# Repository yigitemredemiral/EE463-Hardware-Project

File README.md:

# EE463 Hardware Project: 60 W Synchronous Buck Converter

METU EE463 Static Power Conversion I, Fall 2026, term project
([specification](https://github.com/odtu/EE463/blob/master/Hardware%20Project/EE463%20Hardware%20Project.md)).

20–48 V DC input, 12 V / 5 A (60 W) regulated output, closed-loop peak current-mode control, one input source,
own 4-layer PCB. Bonus targets: 90 W overload, 7.5 A-class current limit, reverse-polarity protection, efficiency,
line/load transient comparison.

| | |
|---|---|
| Topology | Synchronous buck, 94.3 kHz |
| Controller | Analog Devices LTC3895 (150 V, peak current mode), self-supplied from VIN and then from VOUT (EXTVCC) |
| Power stage | Infineon BSC040N08NS5 (high side), BSC026N08NS5 (low side), Coilcraft XAL1510-333 33 µH, 2 × 330 µF polymer |
| Protection | LM74700-Q1 ideal diode (reverse polarity), average current limit 7.88 A (LT6105 + LT6654 + LT1636), RUN/OVLO |
| PCB | 4 layers, 90 × 65 mm, KiCad 10 |
| Simulated efficiency | 97.3 % average at 60 W over 20/24/36/48 V *(simulation, not measured)* |

## Status (19 November 2026)

| Deadline | Item | Status |
|---|---|---|
| 22 Nov | Pre-report | Draft: [`reports/PreReport.md`](reports/PreReport.md) |
| 24–25 Nov | Feedback session | Schematic, PCB and simulations ready |
| 30 Nov | PCB files for sponsored production | Gerber/drill not generated yet (after the feedback session) |
| 4 Jan | Hardware demo | — |

Nothing has been ordered or sent to a manufacturer yet. No hardware measurement exists yet.

## Repository map

| Folder | Content |
|---|---|
| [`hardware/kicad_RevF4/`](hardware/kicad_RevF4/) | **Current board.** RevF2 schematic with the re-routed signals, constant-width power tracks, pad stitching pours and the course PCB-checker fixes. Passes the [course PCB checker](https://github.com/odtu/EE463/tree/master/Hardware%20Project/PCB-Checker) with 0 errors at 5 A and 7.5 A (only warning: 4 layers). Settings and waiver in `pcb_checker.json`. |
| [`hardware/kicad_RevF2/`](hardware/kicad_RevF2/) | KiCad 10 project. The schematic is drawn with wires (one A3 sheet, five blocks); the PCB is the RevF1 layout with 0805 parts, CCATH1 and the new part numbers. Printable copies: [schematic](hardware/kicad_RevF2/EE463_Buck_RevF2_schematic.pdf), [assembly top](hardware/kicad_RevF2/EE463_Buck_RevF2_assembly_top.pdf), [assembly bottom](hardware/kicad_RevF2/EE463_Buck_RevF2_assembly_bottom.pdf). |
| [`simulation/ltspice_RevF2/`](simulation/ltspice_RevF2/) | Drawn LTspice schematic of the final design (`EE463_Buck_RevF2.asc`) with its symbols and models. Open it in LTspice and run. |
| [`simulation/ltspice_RevF1_runs/`](simulation/ltspice_RevF1_runs/) | All RevF1 netlists, logs and scripts behind the numbers in the reports. |
| [`simulation/compensation_AB/`](simulation/compensation_AB/) | Loop-gain and transient comparison of compensation A and B. |
| [`calculations/`](calculations/) | Analytical design (duty cycle, ripple, stresses, losses, thermal). |
| [`bom/`](bom/) | Bill of materials in the course format, full BOM with datasheets, ordering notes. |
| [`reports/FinalReport/`](reports/FinalReport/) | Full report ([PDF](reports/FinalReport/EE463_Final_Report.pdf); design, circuit simulation, PCB and checker, 5-minute thermal analysis). Compile `main.tex` with pdfLaTeX; all numbers come from `values.tex`. PCB-checker reports in `pcb_checker/`. |
| [`simulation/analysis_RevF4/`](simulation/analysis_RevF4/) | Scripts behind the final report: LTspice batch runs, loss breakdown, loop gain, 4-layer thermal model, copper current flow. |
| [`reports/`](reports/) | Pre-report, control-loop section, figures. |
| [`docs/design_review/`](docs/design_review/) | Design review and revision notes (Turkish), RevD5E1 → RevF1 → RevF2. |
| [`tools/`](tools/) | Scripts that generate the schematic, the LTspice drawing, the BOM and run the checks. |

## Revision history

| Revision | Change |
|---|---|
| RevD5E1 | First complete design (Yasin): LTC3895, 145 kHz, Schottky reverse protection |
| RevF1 | Review and two rounds of changes: 94.3 kHz, BSC040 high side, compensation A, current limit 7.88 A, OVLO 58 V, LM74700 ideal diode, hot-loop capacitors, thermal vias, layout fixes |
| RevF2 | Readable schematic (KiCad and LTspice, drawn with wires); 24 of 30 former 0603 parts enlarged to 0805 (course rule) by moving them ≤ 0.38 mm, 6 resistors stay 0603; Vishay parts replaced (course rule: no Israel-made parts); CCATH1 1 µF / 100 V added at the LM74700 CATHODE (approved in the RevF1 review); BOM in the course format with prices and datasheets. ERC 0, DRC 0, parity 0. |
| **RevF4** | Signal re-route; constant track widths; pours instead of pad-to-via tracks; SW and Q2 source pours; course PCB-checker fixes (via-to-drill spacing, no vias in small pads, 0.4 mm via arrays at RS1 and Q2 sources). DRC 0, parity 0. |

## Checks

```bash
bash tools/run_checks.sh
```

- KiCad schematic connectivity = RevF1 netlist (net-by-net comparison), ERC, DRC with schematic parity.
- LTspice drawing: LTspice's own netlist of the `.asc` compared element by element with the RevF1 simulation netlist.

## Tools used

KiCad 10.0, LTspice 26.0, Python 3.12 (numpy, matplotlib). AI tools (Claude) were used for simulation scripting,
schematic drawing and checks; every result was checked against simulation, the datasheets or the netlist, as the
course rules require.

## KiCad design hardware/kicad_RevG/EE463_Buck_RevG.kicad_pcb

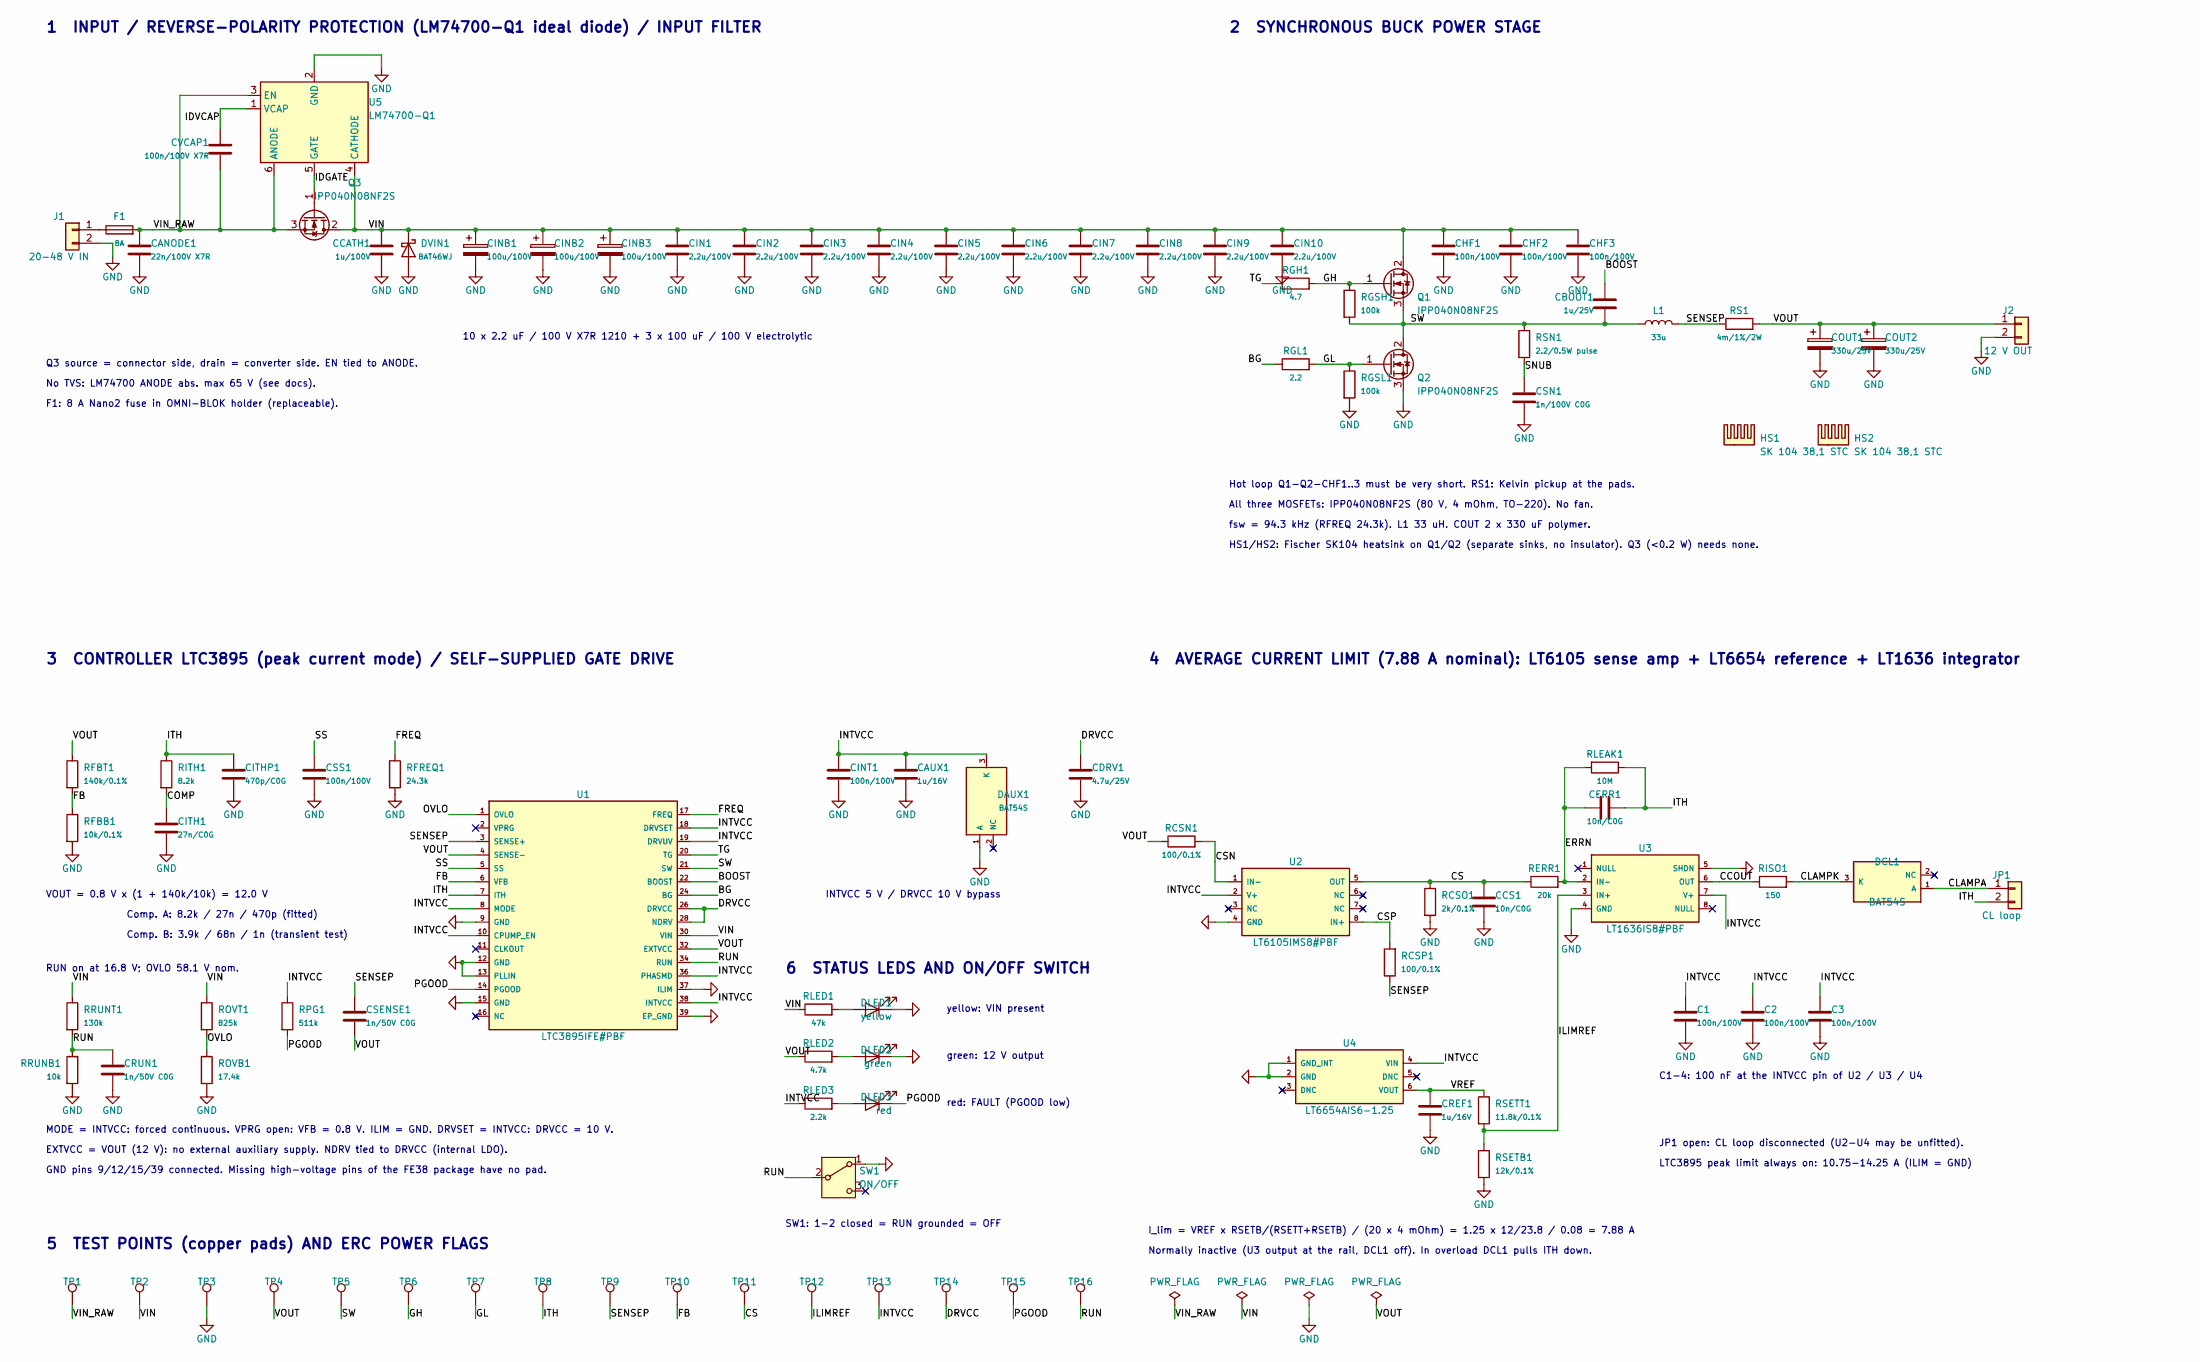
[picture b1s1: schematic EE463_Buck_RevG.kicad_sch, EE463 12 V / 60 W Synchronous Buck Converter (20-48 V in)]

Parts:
C1, C2, C3: 100n/100V; C_0805_2012Metric; MPN C2012X7R2A104K125AA
CANODE1: 22n/100V X7R; C_0805_2012Metric; MPN GRM21BR72A223KA01L
CAUX1: 1u/16V; C_0805_2012Metric; MPN CC0805KKX7R7BB105
CBOOT1: 1u/25V; C_0805_2012Metric; MPN CC0805KKX7R8BB105
CCATH1: 1u/100V; C_0805_2012Metric; MPN C2012X7S2A105K125AB
CCS1: 10n/C0G; C_0805_2012Metric; MPN CL21C103JBFNNNE
CDRV1: 4.7u/25V; C_0805_2012Metric; MPN CL21A475KAQNNNE
CERR1: 10n/C0G; C_0805_2012Metric; MPN CL21C103JBFNNNE
CHF1, CHF2, CHF3: 100n/100V; C_0805_2012Metric; MPN C2012X7R2A104K125AA
CIN1, CIN2, CIN3, CIN4, CIN5, CIN6, CIN7, CIN8, CIN9, CIN10: 2.2u/100V; C_1210_3225Metric; MPN GRM32ER72A225KA35L
CINB1, CINB2, CINB3: 100u/100V; CP_Radial_D10.0mm_P5.00mm; MPN 100ZLH100MEFC10X20
CINT1: 100n/100V; C_0805_2012Metric; MPN C2012X7R2A104K125AA
CITH1: 27n/C0G; C_0805_2012Metric; MPN GRM2165C1H273JA01D
CITHP1: 470p/C0G; C_0805_2012Metric; MPN CL21C471JBANNNC
COUT1, COUT2: 330u/25V; CP_Elec_10x12.6; MPN 25SVPF330M
CREF1: 1u/16V; C_0805_2012Metric; MPN CC0805KKX7R7BB105
CRUN1: 1n/50V C0G; C_0805_2012Metric; MPN CC0805JRNPO9BN102
CSENSE1: 1n/50V C0G; C_0805_2012Metric; MPN CC0805JRNPO9BN102
CSN1: 1n/100V C0G; C_0805_2012Metric; MPN C2012C0G2A102J060AA
CSS1: 100n/100V; C_0805_2012Metric; MPN C2012X7R2A104K125AA
CVCAP1: 100n/100V X7R; C_0805_2012Metric; MPN C2012X7R2A104K125AA
DAUX1: BAT54S; SOT-23; MPN BAT54S-HT
DCL1: BAT54S; SOT-23; MPN BAT54S-HT
DLED1: yellow; LED_0805_2012Metric; MPN 150080YS75000
DLED2: green; LED_0805_2012Metric; MPN 150080GS75000
DLED3: red; LED_0805_2012Metric; MPN 150080RS75000
DVIN1: BAT46WJ; D_SOD-323F; MPN BAT46WJ,115
F1: 8A; Fuseholder_Littelfuse_Nano2_154x; MPN 0154008.DR
HS1, HS2: SK 104 38,1 STC; Heatsink_Fischer_SK104-STC-STIC_35x13mm_2xDrill2.5mm; MPN SK 104 38,1 STC
J1: 20-48 V IN; TerminalBlock_Phoenix_MKDS-1,5-2-5.08_1x02_P5.08mm_Horizont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; MPN 1715721
J2: 12 V OUT; TerminalBlock_Phoenix_MKDS-1,5-2-5.08_1x02_P5.08mm_Horizont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; MPN 1715721
JP1: CL loop; PinHeader_1x02_P2.54mm_Vertical; MPN 61300211121
L1: 33u; L_XAL1510_WE-XHMI1510_Dual; MPN XAL1510-333MED
Q1, Q2, Q3: IPP040N08NF2S; TO-220-3_Vertical; MPN IPP040N08NF2SAKMA1
RCSN1: 100/0.1%; R_0805_2012Metric; MPN TC0525B1000T5G
RCSO1: 2k/0.1%; R_0805_2012Metric; MPN RT0805BRD072KL
RCSP1: 100/0.1%; R_0805_2012Metric; MPN TC0525B1000T5G
RERR1: 20k; R_0805_2012Metric; MPN RC0805FR-0720KL
RFBB1: 10k/0.1%; R_0805_2012Metric; MPN TC0525B1002T5G
RFBT1: 140k/0.1%; R_0805_2012Metric; MPN RT0805BRD07140KL
RFREQ1: 24.3k; R_0805_2012Metric; MPN 0805S8F2432T5E
RGH1: 4.7; R_0805_2012Metric; MPN ERJ-6RQF4R7V
RGL1: 2.2; R_0805_2012Metric; MPN CQ05S8F220KT5E
RGSH1: 100k; R_0805_2012Metric; MPN RC0805FR-07100KL
RGSL1: 100k; R_0805_2012Metric; MPN RC0805FR-07100KL
RISO1: 150; R_0805_2012Metric; MPN 0805S8F1500T5E
RITH1: 8.2k; R_0805_2012Metric; MPN 0805S8F8201T5E
RLEAK1: 10M; R_0805_2012Metric; MPN 0805S8F1005T5E
RLED1: 47k; R_0805_2012Metric; MPN RC0805FR-0747KL
RLED2: 4.7k; R_0805_2012Metric; MPN RC0805FR-074K7L
RLED3: 2.2k; R_0805_2012Metric; MPN RC0805FR-072K2L
ROVB1: 17.4k; R_0805_2012Metric; MPN RC0805FR-0717K4L
ROVT1: 825k; R_0805_2012Metric; MPN 0805S8F8253T5E
RPG1: 511k; R_0805_2012Metric; MPN 0805S8F5113T5E
RRUNB1: 10k; R_0805_2012Metric; MPN 0805S8F1002T5E
RRUNT1: 130k; R_0805_2012Metric; MPN RC0805FR-07130KL
RS1: 4m/1%/2W; R_2512_Shunt_Kelvin_3.05x3.68mm; MPN PA2512FKF7W0R004E
RSETB1: 12k/0.1%; R_0805_2012Metric; MPN RT0805BRD0712KL
RSETT1: 11.8k/0.1%; R_0805_2012Metric; MPN RT0805BRD0711K8L
RSN1: 2.2/0.5W pulse; R_0805_2012Metric; MPN ERJ-P06J2R2V
SW1: ON/OFF; SW_Slide_SPDT_Straight_CK_OS102011MS2Q; MPN OS102011MS2QN1
TP1: VIN_RAW; TestPoint_Pad_D1.5mm; MPN PCB copper pad
TP2: VIN; TestPoint_Pad_D1.5mm; MPN PCB copper pad
TP3: GND; TestPoint_Pad_D1.5mm; MPN PCB copper pad
TP4: VOUT; TestPoint_Pad_D1.5mm; MPN PCB copper pad
TP5: SW; TestPoint_D0p8; MPN PCB copper pad
TP6: GH; TestPoint_D0p8; MPN PCB copper pad
TP7: GL; TestPoint_D0p8; MPN PCB copper pad
TP8: ITH; TestPoint_D0p8; MPN PCB copper pad
TP9: SENSEP; TestPoint_D0p8; MPN PCB copper pad
TP10: FB; TestPoint_D0p8; MPN PCB copper pad
TP11: CS; TestPoint_D0p8; MPN PCB copper pad
TP12: ILIMREF; TestPoint_D0p8; MPN PCB copper pad
TP13: INTVCC; TestPoint_D0p8; MPN PCB copper pad
TP14: DRVCC; TestPoint_D0p8; MPN PCB copper pad
TP15: PGOOD; TestPoint_D0p8; MPN PCB copper pad
TP16: RUN; TestPoint_D0p8; MPN PCB copper pad
U1: LTC3895IFE#PBF; LTC3895_FE38_31_EP39_P0p5; MPN LTC3895IFE#PBF
U2: LT6105IMS8#PBF; MSOP-8_3x3mm_P0.65mm; MPN LT6105IMS8#PBF
U3: LT1636IS8#PBF; SOIC-8_3.9x4.9mm_P1.27mm; MPN LT1636IS8#PBF
U4: LT6654AIS6-1.25; TSOT-23-6; MPN LT6654AIS6-1.25#TRMPBF
U5: LM74700-Q1; SOT-23-6; MPN LM74700QDBVRQ1

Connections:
/BG: RGL1.1, U1.24 (BG)
/BOOST: CBOOT1.1, U1.22 (BOOST)
/CCOUT: RISO1.1, U3.6 (OUT)
/CLAMPA: DCL1.1 (A), JP1.1
/CLAMPK: DCL1.3 (K), RISO1.2
/COMP: CITH1.1, RITH1.2
/CS: CCS1.1, RCSO1.1, RERR1.1, TP11.1 (1_1), U2.5 (OUT)
/CSN: RCSN1.2, U2.1 (IN-)
/CSP: RCSP1.2, U2.8 (IN+)
/DRVCC: CDRV1.1, TP14.1 (1_1), U1.26 (DRVCC), U1.28 (NDRV)
/ERRN: CERR1.2, RERR1.2, RLEAK1.2, U3.2 (IN-)
/FB: RFBB1.1, RFBT1.2, TP10.1 (1_1), U1.6 (VFB)
/FREQ: RFREQ1.1, U1.17 (FREQ)
/GH: Q1.1 (G), RGH1.2, RGSH1.1, TP6.1 (1_1)
/GL: Q2.1 (G), RGL1.2, RGSL1.1, TP7.1 (1_1)
/IDGATE: Q3.1 (G), U5.5 (GATE)
/IDVCAP: CVCAP1.1, U5.1 (VCAP)
/ILIMREF: RSETB1.1, RSETT1.2, TP12.1 (1_1), U3.3 (IN+)
/INTVCC: C1.1, C2.1, C3.1, CAUX1.1, CINT1.1, DAUX1.3 (K), RLED3.1, RPG1.1, TP13.1 (1_1), U1.8 (MODE), U1.10 (CPUMP_EN), U1.18 (DRVSET), U1.19 (DRVUV), U1.36 (PHASMD), U1.38 (INTVCC), U2.2 (V+), U3.7 (V+), U4.4 (VIN)
/ITH: CERR1.1, CITHP1.1, JP1.2, RITH1.1, RLEAK1.1, TP8.1 (1_1), U1.7 (ITH)
/OVLO: ROVB1.1, ROVT1.2, U1.1 (OVLO)
/PGOOD: DLED3.1 (K), RPG1.2, TP15.1 (1_1), U1.14 (PGOOD)
/RUN: CRUN1.1, RRUNB1.1, RRUNT1.2, SW1.2 (B), TP16.1 (1_1), U1.34 (RUN)
/SENSEP: CSENSE1.1, L1.2, RCSP1.1, RS1.1, TP9.1 (1_1), U1.3 (SENSE+)
/SNUB: CSN1.1, RSN1.2
/SS: CSS1.1, U1.5 (SS)
/SW: CBOOT1.2, L1.1, Q1.3 (S), Q2.2 (D), RGSH1.2, RSN1.1, TP5.1 (1_1), U1.21 (SW)
/TG: RGH1.1, U1.20 (TG)
/VIN: CCATH1.1, CHF1.1, CHF2.1, CHF3.1, CIN1.1, CIN2.1, CIN3.1, CIN4.1, CIN5.1, CIN6.1, CIN7.1, CIN8.1, CIN9.1, CIN10.1, CINB1.1, CINB2.1, CINB3.1, DVIN1.1 (K), Q1.2 (D), Q3.2 (D), RLED1.1, ROVT1.1, RRUNT1.1, TP2.1 (1_1), U1.30 (VIN), U5.4 (CATHODE)
/VIN_RAW: CANODE1.1, CVCAP1.2, F1.2, Q3.3 (S), TP1.1 (1_1), U5.3 (EN), U5.6 (ANODE)
/VOUT: COUT1.1, COUT2.1, CSENSE1.2, J2.1, RCSN1.1, RFBT1.1, RLED2.1, RS1.2, TP4.1 (1_1), U1.4 (SENSE-), U1.32 (EXTVCC)
/VREF: CREF1.1, RSETT1.1, U4.6 (VOUT)
GND: C1.2, C2.2, C3.2, CANODE1.2, CAUX1.2, CCATH1.2, CCS1.2, CDRV1.2, CHF1.2, CHF2.2, CHF3.2, CIN1.2, CIN2.2, CIN3.2, CIN4.2, CIN5.2, CIN6.2, CIN7.2, CIN8.2, CIN9.2, CIN10.2, CINB1.2, CINB2.2, CINB3.2, CINT1.2, CITH1.2, CITHP1.2, COUT1.2, COUT2.2, CREF1.2, CRUN1.2, CSN1.2, CSS1.2, DAUX1.1 (A), DLED1.1 (K), DLED2.1 (K), DVIN1.2 (A), J1.2, J2.2, Q2.3 (S), RCSO1.2, RFBB1.2, RFREQ1.2, RGSL1.2, ROVB1.2, RRUNB1.2, RSETB1.2, SW1.1 (A), TP3.1 (1_1), U1.9 (GND), U1.12 (GND), U1.13 (PLLIN), U1.15 (GND), U1.37 (ILIM), U1.39 (EP_GND), U2.4 (GND), U3.4 (GND), U3.5 (SHDN), U4.1 (GND_INT), U4.2 (GND), U5.2 (GND)
unnamed: DLED1.2 (A), RLED1.2
unnamed: DLED2.2 (A), RLED2.2
unnamed: DLED3.2 (A), RLED3.2
unnamed: F1.1, J1.1

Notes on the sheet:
1 INPUT / REVERSE-POLARITY PROTECTION (LM74700-Q1 ideal diode) / INPUT FILTER
Q3 source = connector side, drain = converter side. EN tied to ANODE.
No TVS: LM74700 ANODE abs. max 65 V (see docs).
F1: 8 A Nano2 fuse in OMNI-BLOK holder (replaceable).
10 x 2.2 uF / 100 V X7R 1210 + 3 x 100 uF / 100 V electrolytic
2 SYNCHRONOUS BUCK POWER STAGE
HS1/HS2: Fischer SK104 heatsink on Q1/Q2 (separate sinks, no insulator). Q3 (<0.2 W) needs none.
Hot loop Q1-Q2-CHF1..3 must be very short. RS1: Kelvin pickup at the pads.
All three MOSFETs: IPP040N08NF2S (80 V, 4 mOhm, TO-220). No fan.
fsw = 94.3 kHz (RFREQ 24.3k). L1 33 uH. COUT 2 x 330 uF polymer.
3 CONTROLLER LTC3895 (peak current mode) / SELF-SUPPLIED GATE DRIVE
MODE = INTVCC: forced continuous. VPRG open: VFB = 0.8 V. ILIM = GND. DRVSET = INTVCC: DRVCC = 10 V.
EXTVCC = VOUT (12 V): no external auxiliary supply. NDRV tied to DRVCC (internal LDO).
GND pins 9/12/15/39 connected. Missing high-voltage pins of the FE38 package have no pad.
VOUT = 0.8 V x (1 + 140k/10k) = 12.0 V
Comp. A: 8.2k / 27n / 470p (fitted)
Comp. B: 3.9k / 68n / 1n (transient test)
RUN on at 16.8 V; OVLO 58.1 V nom.
INTVCC 5 V / DRVCC 10 V bypass
4 AVERAGE CURRENT LIMIT (7.88 A nominal): LT6105 sense amp + LT6654 reference + LT1636 integrator
JP1 open: CL loop disconnected (U2-U4 may be unfitted).
LTC3895 peak limit always on: 10.75-14.25 A (ILIM = GND)
I_lim = VREF x RSETB/(RSETT+RSETB) / (20 x 4 mOhm) = 1.25 x 12/23.8 / 0.08 = 7.88 A
Normally inactive (U3 output at the rail, DCL1 off). In overload DCL1 pulls ITH down.
C1-4: 100 nF at the INTVCC pin of U2 / U3 / U4
6 STATUS LEDS AND ON/OFF SWITCH
yellow: VIN present
green: 12 V output
red: FAULT (PGOOD low)
SW1: 1-2 closed = RUN grounded = OFF
5 TEST POINTS (copper pads) AND ERC POWER FLAGS

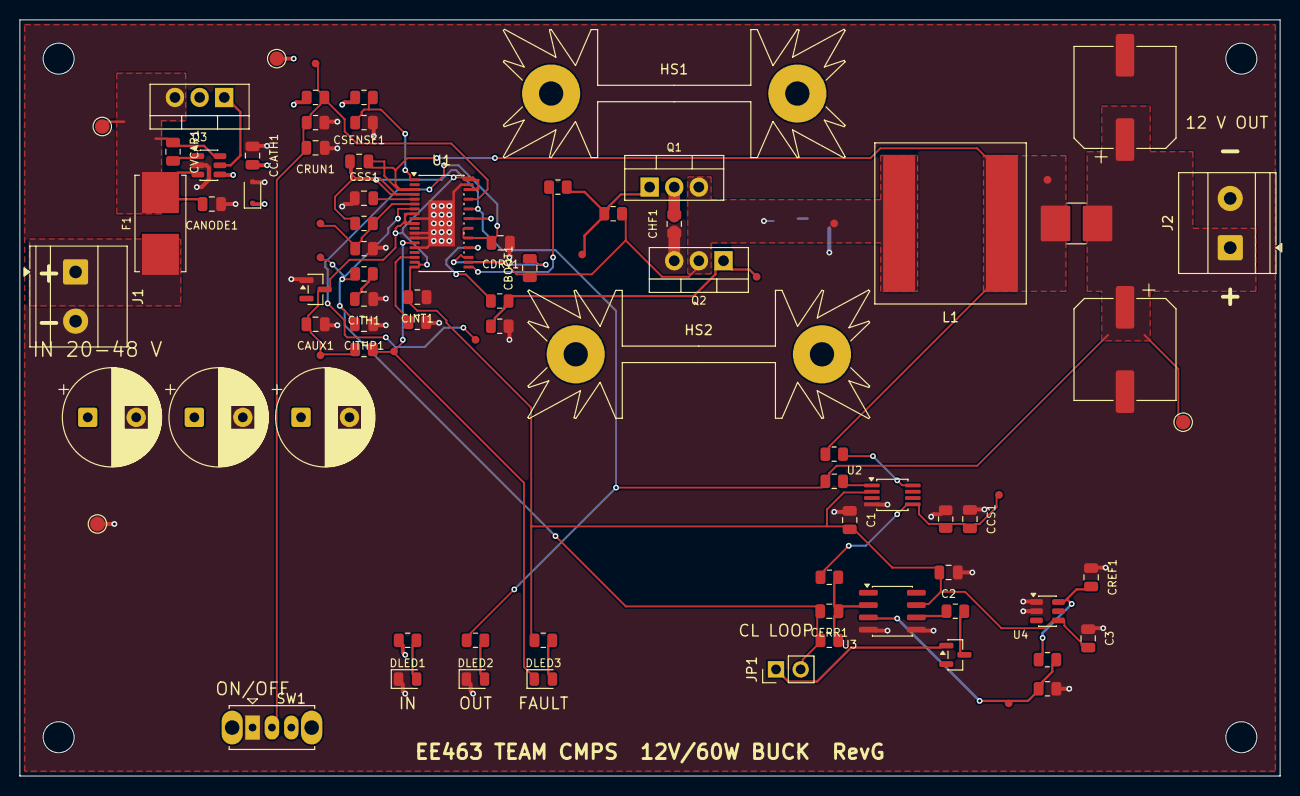
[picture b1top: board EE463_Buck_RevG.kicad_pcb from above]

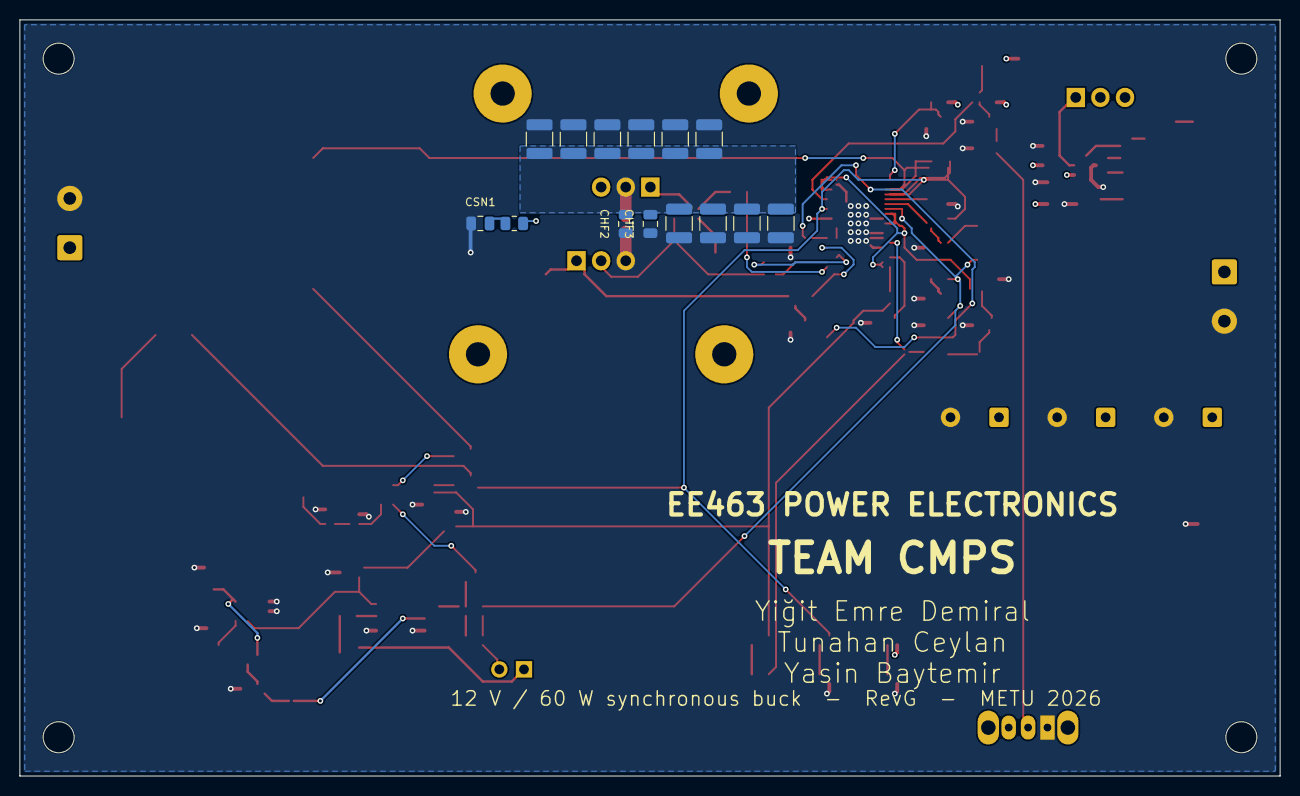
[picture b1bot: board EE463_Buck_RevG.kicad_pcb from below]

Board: 4 copper layers, 130.0 x 78.0 mm, 105 parts (14 on the bottom side), 37 nets.

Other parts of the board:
H1, H2, H3, H4: MountingHole_3.2mm_M3

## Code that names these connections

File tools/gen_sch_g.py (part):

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    s.put('Q3', 76.2, 58.42, 270)
    s.put('U5', 76.2, 40.64, 0, 'x')
    s.hpart('F1', s.pin('J1', 1)[0], Y)                                   # input fuse
    s.w(s.pin('F1', 2), s.pin('Q3', 1))                                  # VIN_RAW line
    s.lab('VIN_RAW', (45.72, Y))
    s.vpart('CANODE1', 43.18, Y); s.gnd((43.18, Y + 7.62))
    s.w(s.pin('U5', 3), (50.8, s.pin('U5', 3)[1]), (50.8, Y))       # EN -> ANODE
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    s.vpart('CBOOT1', 320.04, 71.12); s.w((320.04, 71.12), (320.04, 68.58)); s.lab('BOOST', (320.04, 68.58))
    # inductor, shunt, output
    s.put('RS1', 345.44, SW, 90)
    s.w(s.pin('L1', 2), s.pin('RS1', 1)); s.lab('SENSEP', (335.28, SW))
    VO = s.pin('RS1', 2)
    s.w(VO, (393.7, SW)); s.lab('VOUT', (351.79, SW))
    for x, ref in ((360.68, 'COUT1'), (370.84, 'COUT2')):
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          32: 'VOUT', 34: 'RUN', 36: 'INTVCC', 38: 'INTVCC'}
    for n, name in Rt.items():
        s.stub_label('U1', n, name, dx=5.08)
    p = s.pin('U1', 28); s.w(p, (p[0] + 2.54, p[1]), (p[0] + 2.54, s.pin('U1', 26)[1]))   # NDRV tied to DRVCC
    s.stub_gnd('U1', 37, dx=2.54)
    s.stub_gnd('U1', 39, dx=2.54)
    T('MODE = INTVCC: forced continuous. VPRG open: VFB = 0.8 V. ILIM = GND. DRVSET = INTVCC: DRVCC = 10 V.', 25.4, 231.14)
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    q = s.pin('U2', 1); s.w(q, (246.38, q[1]), (246.38, 176.53))
    s.hpart('RCSN1', 236.22, 176.53, pin1_left=True); s.w(s.pin('RCSN1', 2), (246.38, 176.53))
    s.lab('CSN', (246.38, 180.34))
    s.stub_label('RCSN1', 1, 'VOUT', dx=-2.54)
    s.stub_label('U2', 2, 'INTVCC', dx=-5.08)
    s.nc('U2', 3); s.nc('U2', 6); s.nc('U2', 7)
    g = s.pin('U2', 4); s.w(g, (g[0] - 2.54, g[1])); s.gnd((g[0] - 2.54, g[1]), 270)
    q = s.pin('U2', 8); s.w(q, (279.4, q[1]), (279.4, 195.58)); s.lab('CSP', (276.86, q[1]))
    s.vpart('RCSP1', 279.4, 195.58, flip=True); s.w((279.4, 203.2), (279.4, 205.74)); s.lab('SENSEP', (279.4, 205.74))
    CS = s.pin('U2', 5)[1]
    s.w(s.pin('U2', 5), (304.8, CS)); s.lab('CS', (290.83, CS))
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    s.w((323.85, 162.56), (327.66, 162.56), (327.66, 170.18))
    s.w((323.85, 170.18), (332.74, 170.18)); s.lab('ITH', (332.74, 170.18))
    s.nc('U3', 1); s.nc('U3', 8)
    q = s.pin('U3', 3); s.w(q, (311.15, q[1]), (311.15, 231.14), (297.18, 231.14)); s.lab('ILIMREF', (311.15, 213.36))
    g = s.pin('U3', 4); s.w(g, (313.69, g[1]), (313.69, 193.04)); s.gnd((313.69, 193.04))
    s.stub_gnd('U3', 5, dx=5.08)
    s.hpart('RISO1', 347.98, 184.15, pin1_left=True); s.w(s.pin('U3', 6), s.pin('RISO1', 1)); s.lab('CCOUT', (341.63, 184.15))
    s.put('DCL1', 373.38, 184.15, 180)
    s.w(s.pin('RISO1', 2), s.pin('DCL1', 3)); s.lab('CLAMPK', (356.87, 184.15))
    q = s.pin('DCL1', 1); s.put('JP1', q[0] + 15.24, q[1])
    s.w(q, s.pin('JP1', 1)); s.lab('CLAMPA', (q[0] + 2.54, q[1]))
    s.stub_label('JP1', 2, 'ITH', dx=-2.54)
    T('JP1 open: CL loop disconnected (U2-U4 may be unfitted).', 330.2, 233.68)
    T('LTC3895 peak limit always on: 10.75-14.25 A (ILIM = GND)', 330.2, 237.49)
    s.nc('DCL1', 2)
    q = s.pin('U3', 7); s.w(q, (342.9, q[1]), (342.9, 193.04)); s.lab('INTVCC', (342.9, 193.04))
    s.put('U4', 271.78, 220.98)
    a, b = s.pin('U4', 1), s.pin('U4', 2)
    s.w(a, (256.54, a[1]), (256.54, b[1]), b); s.w((256.54, b[1]), (254.0, b[1])); s.gnd((254.0, b[1]), 270)
    s.nc('U4', 3); s.nc('U4', 5)
    s.stub_label('U4', 4, 'INTVCC', dx=5.08)
    s.w(s.pin('U4', 6), (297.18, 223.52)); s.lab('VREF', (290.83, 223.52))
    s.vpart('CREF1', 287.02, 223.52); s.gnd((287.02, 231.14))
    s.vpart('RSETT1', 297.18, 223.52)
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
    for k, x in ((2, 335.28), (3, 347.98), (4, 360.68)):          # U2/U3/U4 supply decoupling
        s.vpart(f'C{k - 1}', x, 205.74); s.w((x, 205.74), (x, 203.2)); s.lab('INTVCC', (x, 203.2)); s.gnd((x, 213.36))
    T('C1-4: 100 nF at the INTVCC pin of U2 / U3 / U4', 330.2, 220.98)

    # ======================= 6  STATUS LEDS / ON-OFF SWITCH ======================
    T('6  STATUS LEDS AND ON/OFF SWITCH', 165.1, 200.66, 2.0, True)
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        s.lab(end, e) if end else s.gnd(e, 90)
        T(txt, x0 + 30.48, y)
    s.put('SW1', 175.26, 240.03)
    s.stub_label('SW1', 2, 'RUN', dx=-5.08)
    s.stub_gnd('SW1', 1, dx=2.54)
    s.nc('SW1', 3)
    T('SW1: 1-2 closed = RUN grounded = OFF', 165.1, 248.92)
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
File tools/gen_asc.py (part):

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    a.sym('res', 'RGSL1', '100k', (1408, q2g[1]), 'R0', pin=1); a.gnd(a.pin('RGSL1', 2))
    # snubber, bootstrap
    a.sym('res', 'RSN1', '2.2', (1680, SW), 'R0', pin=1)
    p = a.pin('RSN1', 2); a.flag(p, 'SNUB')
    a.sym('cap', 'CSN1', '1n', p, 'R0', pin=1); a.gnd(a.pin('CSN1', 2))
    a.sym('cap', 'CBOOT1', '1u', (1584, SW), 'R180', pin=2)
    a.flag(a.pin('CBOOT1', 1), 'BOOST')
    # inductor, trace, shunt, output
    e = a.h('ind', 'L1', '33u Rser=20m', (1776, SW))
    a.flag(e, 'LOUT'); e = a.h('res', 'Rtrace', '3m', e)
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    chain(1376, 1408, [('res', 'RRUNT1', '130k', 'RUN'), ('res', 'RRUNB1', '10k', None)], 'IN')
    a.w(a.pin('RRUNT1', 2), (1472, a.pin('RRUNT1', 2)[1])); chain(1472, a.pin('RRUNT1', 2)[1], [('cap', 'CRUN1', '1n', None)])
    chain(1600, 1408, [('res', 'ROVT1', '825k', 'OVLO'), ('res', 'ROVB1', '17.4k', None)], 'IN')
    chain(1760, 1408, [('res', 'RPG1', '511k', None)], 'INTVCC', gnd_end=False); a.flag(a.pin('RPG1', 2), 'PGOOD')
    chain(1888, 1408, [('cap', 'CSENSE1', '1n', None)], 'SENSEP', gnd_end=False); a.flag(a.pin('CSENSE1', 2), 'OUT')
    T(1312, 1344, ';RUN on at 16.8 V, OVLO 58.1 V', 2)
    a.w((1376, 1792), (1664, 1792)); a.w((1376, 1760), (1376, 1792)); a.flag((1376, 1760), 'INTVCC')
    chain(1472, 1792, [('cap', 'CINT1', '0.1u', None)])
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    a.items.append(('LT6105', 'XU2', 'LT6105', (2560, 1184), 'R0', ())); a.pos['XU2'] = ('LT6105', (2560, 1184), 'R0')
    a.items.append(('LT1636', 'XU3', 'LT1636', (3104, 1184), 'R0', ())); a.pos['XU3'] = ('LT1636', (3104, 1184), 'R0')
    a.items.append(('LT6654', 'XU4', 'LT6654-1.25', (2560, 1600), 'R0', ())); a.pos['XU4'] = ('LT6654', (2560, 1600), 'R0')
    p = a.pin('XU2', 6); a.sym('res', 'RCSP1', '100', p, 'R90', pin=1); a.flag(a.pin('RCSP1', 2), 'SENSEP')
    a.flag(p, 'CSP')
    p = a.pin('XU2', 1); a.sym('res', 'RCSN1', '100', p, 'R90', pin=1); a.flag(a.pin('RCSN1', 2), 'OUT')
    a.flag(p, 'CSN')
    p = a.pin('XU2', 2); a.flag(a.w(p, (p[0], p[1] - 32)), 'INTVCC')
    a.gnd(a.pin('XU2', 3))
    cs = a.pin('XU2', 4)
    a.w(cs, (2720, cs[1]), (2816, cs[1]), (2896, cs[1])); a.flag((2720, cs[1]), 'CS')
    chain(2720, cs[1], [('res', 'RCSO1', '2k', None)])
    chain(2816, cs[1], [('cap', 'CCS1', '10n', None)])
    a.sym('res', 'RERR1', '20k', (2896, cs[1]), 'R270', pin=1)
    errn = a.pin('RERR1', 2)
    m = a.pin('XU3', 2)
    a.w(errn, (2992, errn[1]), (2992, m[1]), m); a.flag((2992, m[1]), 'ERRN')
    a.w((2992, errn[1]), (2992, 928))
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    a.w((2992, 928), (2992, 864)); a.sym('res', 'RLEAK1', '10Meg', (2992, 864), 'R90', pin=2)
    a.w(a.pin('CERR1', 1), (3168, 928)); a.w(a.pin('RLEAK1', 1), (3168, 864), (3168, 928), (3232, 928))
    a.flag((3232, 928), 'ITH')
    a.flag(a.pin('XU3', 1), 'ILIMREF')
    p = a.pin('XU3', 3); a.flag(a.w(p, (p[0], p[1] - 32)), 'INTVCC')
    a.gnd(a.pin('XU3', 4)); a.gnd(a.pin('XU3', 6))
    o = a.pin('XU3', 5); a.flag(o, 'CCOUT')
    a.sym('res', 'RISO1', '150', o, 'R270', pin=1)
    k = a.pin('RISO1', 2); a.flag(k, 'CLAMPK')
    a.sym('schottky', 'DCL1', 'BAT54', k, 'R90', pin=2)
    a.flag(a.pin('DCL1', 1), 'ITH')
    p = a.pin('XU4', 2); a.flag(a.w(p, (p[0] - 32, p[1])), 'INTVCC')
    a.gnd(a.pin('XU4', 1))
    vr = a.pin('XU4', 3); a.w(vr, (2752, vr[1]), (2848, vr[1])); a.flag((2752, vr[1]), 'VREF')
    chain(2752, vr[1], [('cap', 'CREF1', '1u', None)])
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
